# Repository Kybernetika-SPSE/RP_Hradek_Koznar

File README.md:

# KYB Model větrné elektrárny

## Zadání projektu
Model větrné elektrárny

## Řešitelský tým
Štěpán Kožnar, Josef Hrádek

## Vedoucí
Jiří Švihla

## Oponent
Ing. Pavel Jedlička

## Shrnutí projektu
Funkční edukativní model vyrobený z HT potrubí a 3D tištěných PET dílů. Model simuluje přenos energie pomocí systému dvou motorů (motor-generátor) v uzavřené "strojní kleci". Dále zprostředkovává měrění výstupu a popisuje další změny při zpracovávání elektrické energie.

https://discord.gg/VVhzTzu8

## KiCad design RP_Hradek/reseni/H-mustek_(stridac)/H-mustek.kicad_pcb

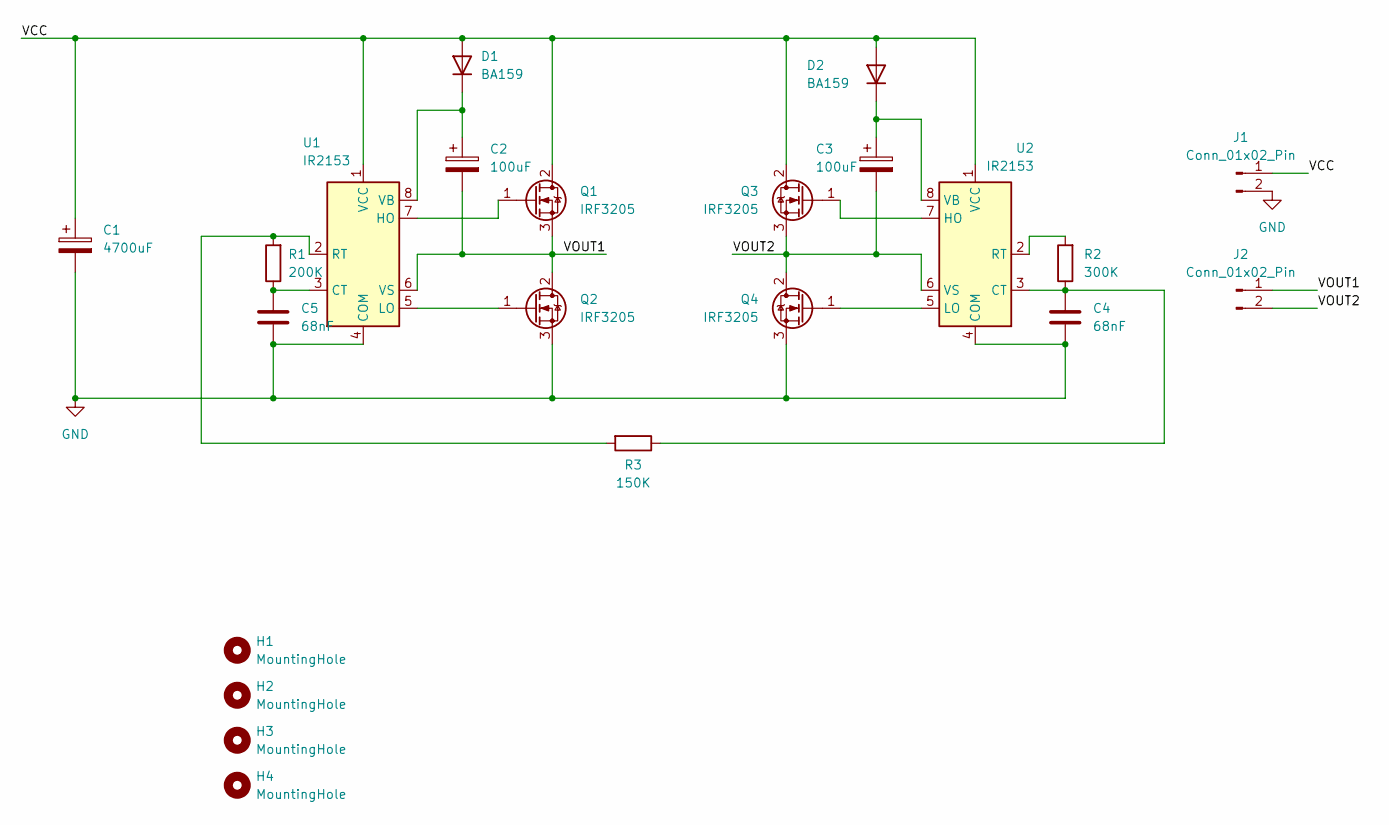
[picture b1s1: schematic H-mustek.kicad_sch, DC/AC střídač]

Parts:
C1: 4700uF; CP_Radial_D16.0mm_P7.50mm
C2, C3: 100uF; CP_Radial_D8.0mm_P3.50mm
C4, C5: 68nF; C_Axial_L3.8mm_D2.6mm_P7.50mm_Horizontal
D1, D2: BA159; D_DO-41_SOD81_P3.81mm_Vertical_AnodeUp
H1, H2, H3, H4: MountingHole; MountingHole_3.2mm_M3
J1: Conn_01x02_Pin; AMASS_XT30UPB-F_1x02_P5.0mm_Vertical
J2: Conn_01x02_Pin; SolderWire-2.5sqmm_1x02_P7.2mm_D2.4mm_OD3.6mm
Q1, Q2, Q3, Q4: IRF3205; TO-263-3_TabPin2
R1: 200K; R_Axial_DIN0207_L6.3mm_D2.5mm_P7.62mm_Horizontal
R2: 300K; R_Axial_DIN0207_L6.3mm_D2.5mm_P7.62mm_Horizontal
R3: 150K; R_Axial_DIN0207_L6.3mm_D2.5mm_P7.62mm_Horizontal
U1, U2: IR2153; DIP-8_W7.62mm

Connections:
/VCC: C1.1, D1.2 (A), D2.2 (A), J1.1, Q1.2 (D), Q3.2 (D), U1.1 (VCC), U2.1 (VCC)
/VOUT1: C2.2, J2.1, Q1.3 (S), Q2.2 (D), U1.6 (VS)
/VOUT2: C3.2, J2.2, Q3.3 (S), Q4.2 (D), U2.6 (VS)
GND: C1.2, C4.2, C5.2, J1.2, Q2.3 (S), Q4.3 (S), U1.4 (COM), U2.4 (COM)
unnamed: C2.1, D1.1 (K), U1.8 (VB)
unnamed: C3.1, D2.1 (K), U2.8 (VB)
unnamed: Q1.1 (G), U1.7 (HO)
unnamed: Q2.1 (G), U1.5 (LO)
unnamed: Q3.1 (G), U2.7 (HO)
unnamed: Q4.1 (G), U2.5 (LO)
unnamed: C5.1, R1.1, U1.3 (CT)
unnamed: R1.2, R3.2, U1.2 (RT)
unnamed: C4.1, R2.1, R3.1, U2.3 (CT)
unnamed: R2.2, U2.2 (RT)

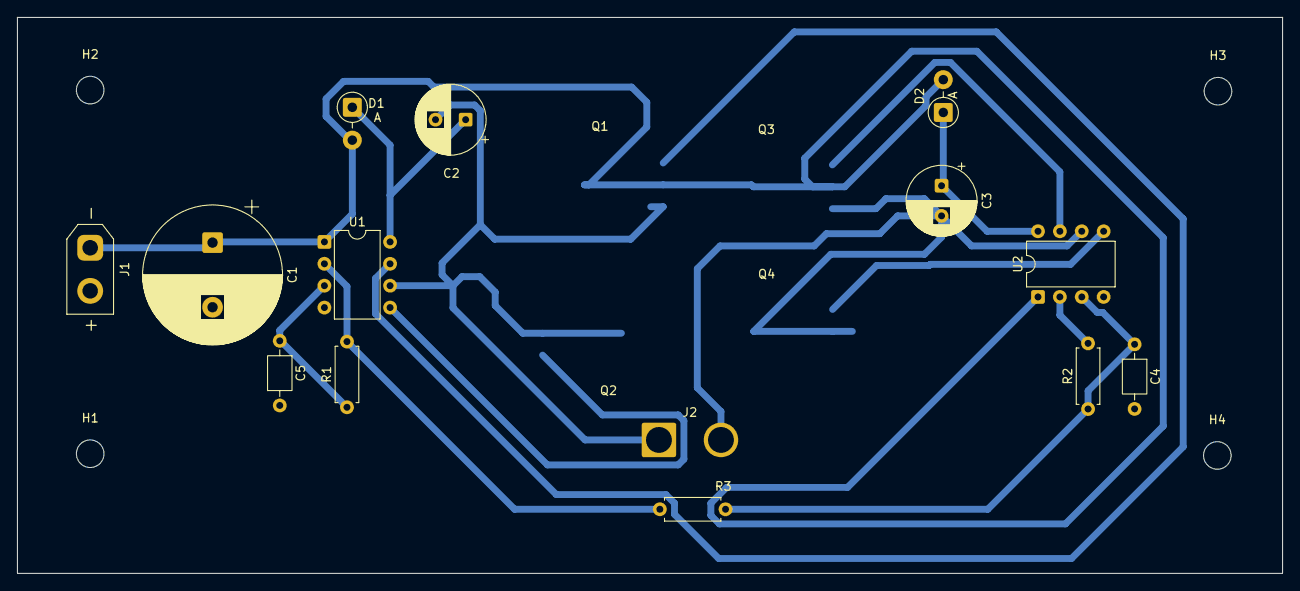
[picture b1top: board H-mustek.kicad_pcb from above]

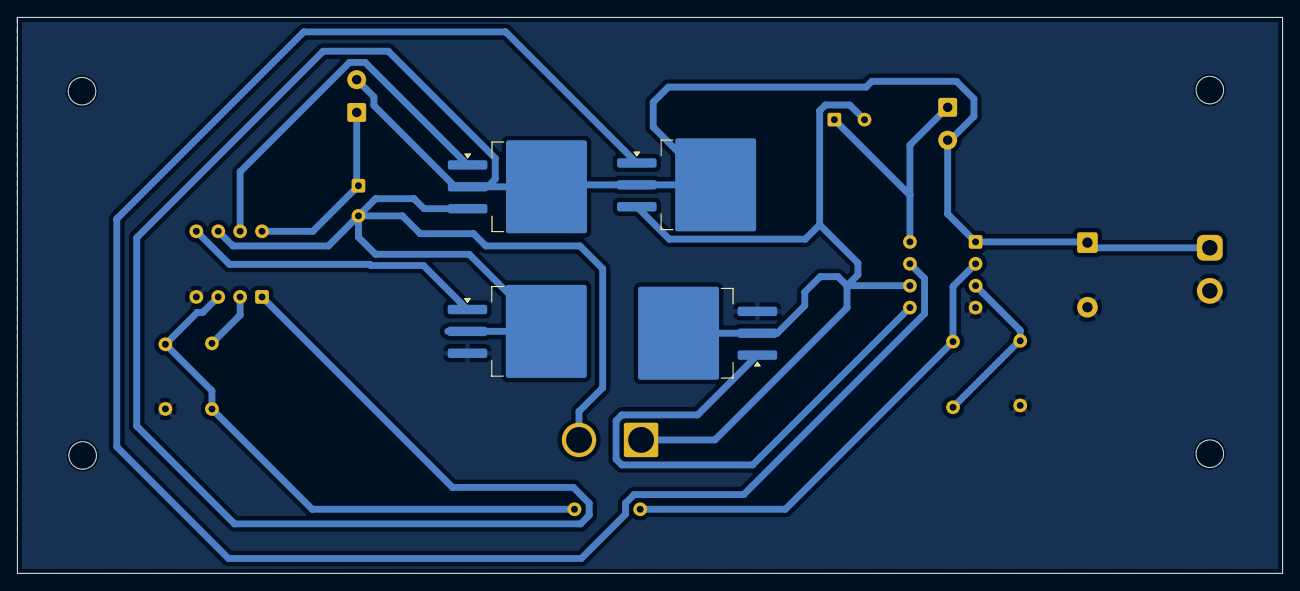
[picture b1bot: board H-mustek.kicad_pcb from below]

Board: 2 copper layers, 146.8 x 64.5 mm, 22 parts (4 on the bottom side), 14 nets.

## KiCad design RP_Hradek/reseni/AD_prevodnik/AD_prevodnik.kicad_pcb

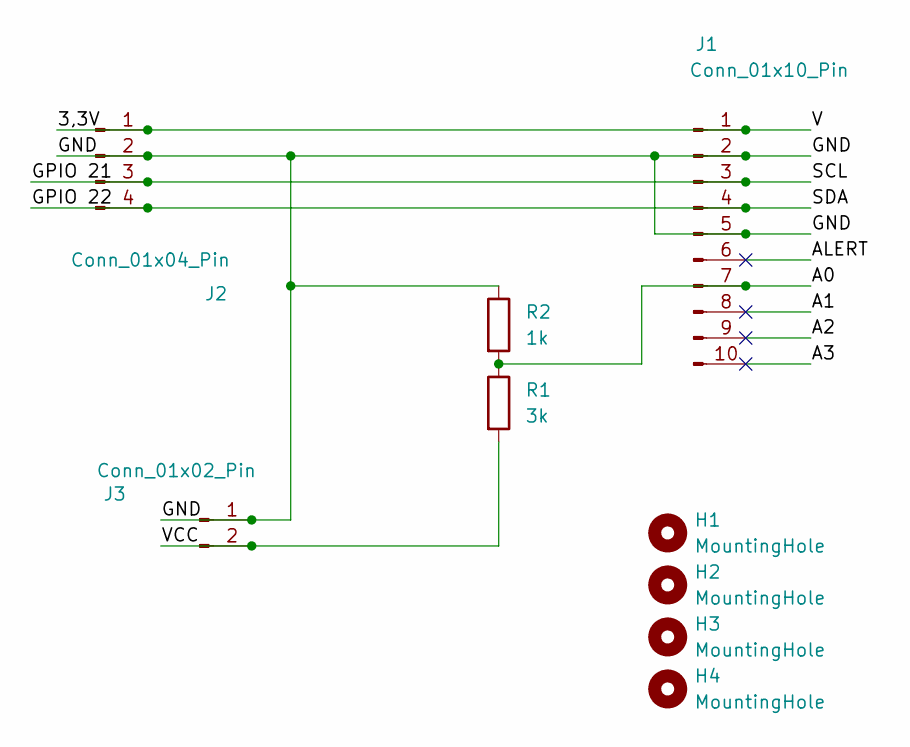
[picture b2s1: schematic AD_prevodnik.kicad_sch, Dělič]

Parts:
H1, H2, H3, H4: MountingHole; MountingHole_2.2mm_M2
J1: Conn_01x10_Pin; PinHeader_1x10_P2.54mm_Vertical
J2: Conn_01x04_Pin; PinHeader_1x04_P2.54mm_Vertical
J3: Conn_01x02_Pin; AMASS_XT30UPB-F_1x02_P5.0mm_Vertical
R1: 3k; R_Axial_DIN0204_L3.6mm_D1.6mm_P5.08mm_Horizontal
R2: 1k; R_Axial_DIN0204_L3.6mm_D1.6mm_P5.08mm_Horizontal

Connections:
/3,3V: J1.1, J2.1
/A0: J1.7, R1.1, R2.2
/A1: J1.8
/A2: J1.9
/A3: J1.10
/ALERT: J1.6
/GND: J1.2, J1.5, J2.2, J3.1, R2.1
/GPIO 21: J1.3, J2.3
/GPIO 22: J1.4, J2.4
/VCC: J3.2, R1.2

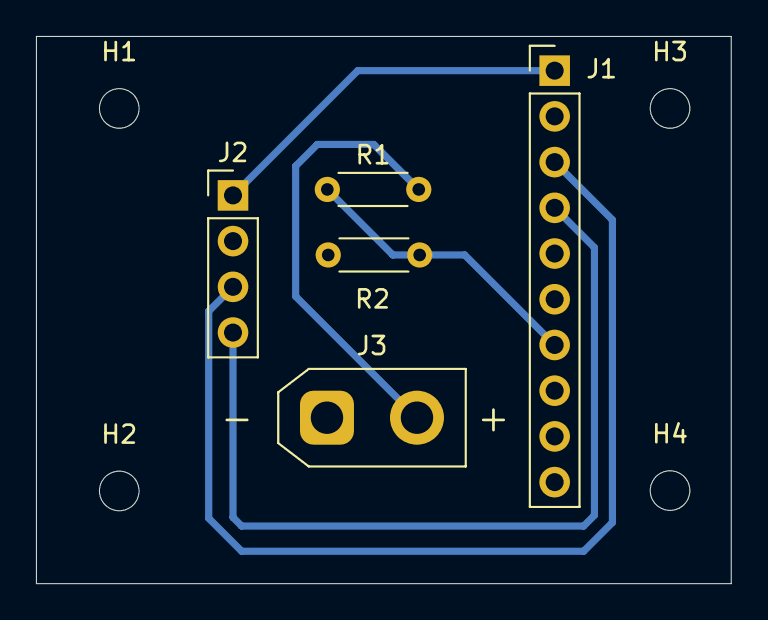
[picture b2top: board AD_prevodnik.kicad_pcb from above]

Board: 2 copper layers, 38.6 x 30.4 mm, 9 parts (0 on the bottom side), 6 nets.

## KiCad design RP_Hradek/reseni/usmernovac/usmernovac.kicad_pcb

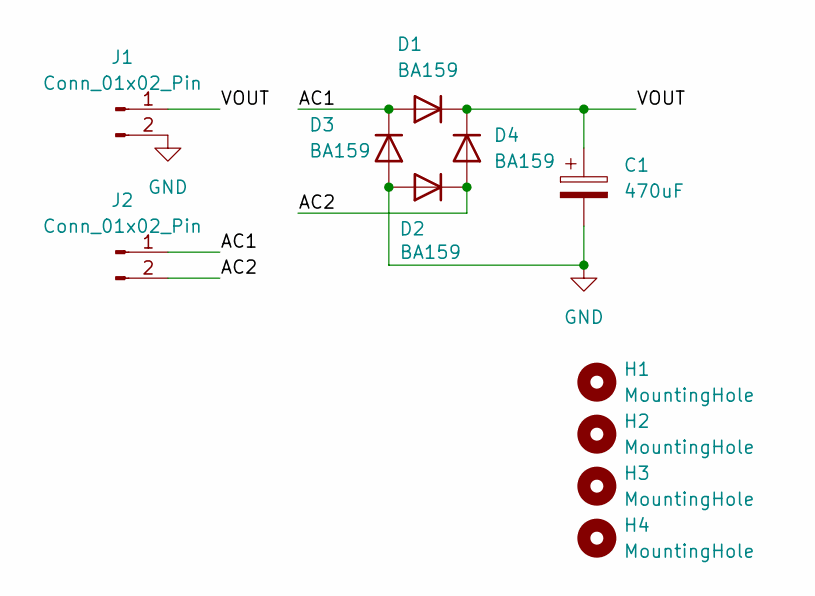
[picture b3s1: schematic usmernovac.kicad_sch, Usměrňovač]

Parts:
C1: 470uF; CP_Radial_D8.0mm_P5.00mm
D1, D2, D3, D4: BA159; D_DO-41_SOD81_P10.16mm_Horizontal
H1, H2, H3, H4: MountingHole; MountingHole_2.2mm_M2
J1, J2: Conn_01x02_Pin; SolderWire-2sqmm_1x02_P7.8mm_D2mm_OD3.9mm

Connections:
/AC1: D1.2 (A), D3.1 (K), J2.1
/AC2: D2.1 (K), D4.2 (A), J2.2
/VOUT: C1.1, D1.1 (K), D4.1 (K), J1.1
GND: C1.2, D2.2 (A), D3.2 (A), J1.2

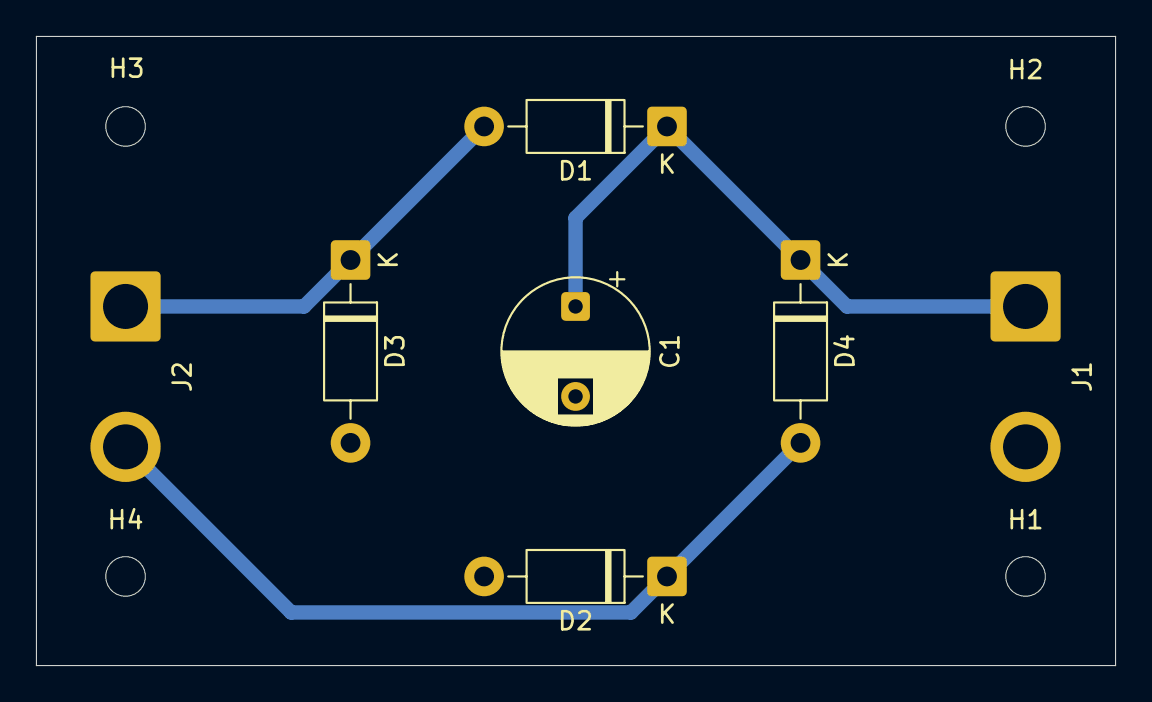
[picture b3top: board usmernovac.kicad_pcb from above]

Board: 2 copper layers, 60.0 x 35.0 mm, 11 parts (0 on the bottom side), 4 nets.

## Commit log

2025-11-23 testovani
2025-12-19 test
2026-01-11 motor
2026-02-10 díly
2026-03-19 M a U poprve
2026-04-13 130426
2026-04-20 200426
2026-04-21 210426
2026-04-26 260426
2026-04-28 280426
2026-04-30 repo ready k odevzdani¨
2026-04-30 readme
